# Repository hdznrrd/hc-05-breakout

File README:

HC-05 Breakout

Breakout board for the popular HC-05 Bluetooth 2.0 module.

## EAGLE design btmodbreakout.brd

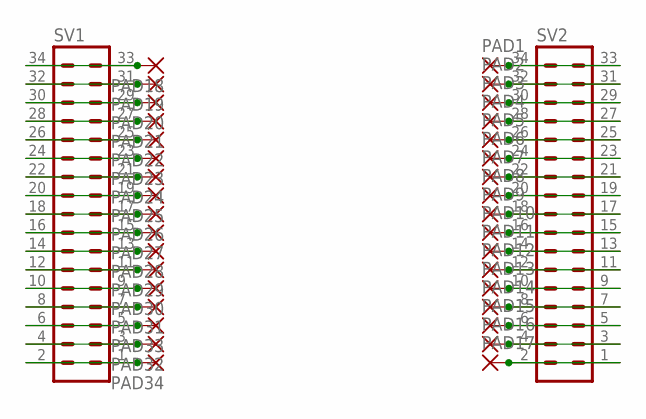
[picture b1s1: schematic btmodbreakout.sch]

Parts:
PAD1, PAD2, PAD3, PAD4, PAD5, PAD6, PAD7, PAD8, PAD9, PAD10, PAD11, PAD12, PAD13, PAD14, PAD15, PAD16, PAD17, PAD18, PAD19, PAD20, PAD21, PAD22, PAD23, PAD24, PAD25, PAD26, PAD27, PAD28, PAD29, PAD30, PAD31, PAD32, PAD33, PAD34: SMD2; SMD1,27-2,54
SV1, SV2: MA17-2

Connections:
unnamed: PAD18.1, SV1.33, SV1.34
unnamed: PAD19.1, SV1.31, SV1.32
unnamed: PAD20.1, SV1.29, SV1.30
unnamed: PAD21.1, SV1.27, SV1.28
unnamed: PAD22.1, SV1.25, SV1.26
unnamed: PAD23.1, SV1.23, SV1.24
unnamed: PAD24.1, SV1.21, SV1.22
unnamed: PAD25.1, SV1.19, SV1.20
unnamed: PAD26.1, SV1.17, SV1.18
unnamed: PAD27.1, SV1.15, SV1.16
unnamed: PAD28.1, SV1.13, SV1.14
unnamed: PAD29.1, SV1.11, SV1.12
unnamed: PAD30.1, SV1.9, SV1.10
unnamed: PAD31.1, SV1.7, SV1.8
unnamed: PAD33.1, SV1.5, SV1.6
unnamed: PAD32.1, SV1.3, SV1.4
unnamed: PAD34.1, SV1.1, SV1.2
unnamed: PAD1.1, SV2.33, SV2.34
unnamed: PAD2.1, SV2.31, SV2.32
unnamed: PAD3.1, SV2.29, SV2.30
unnamed: PAD4.1, SV2.27, SV2.28
unnamed: PAD5.1, SV2.25, SV2.26
unnamed: PAD6.1, SV2.23, SV2.24
unnamed: PAD7.1, SV2.21, SV2.22
unnamed: PAD8.1, SV2.19, SV2.20
unnamed: PAD9.1, SV2.17, SV2.18
unnamed: PAD10.1, SV2.15, SV2.16
unnamed: PAD11.1, SV2.13, SV2.14
unnamed: PAD12.1, SV2.11, SV2.12
unnamed: PAD13.1, SV2.9, SV2.10
unnamed: PAD14.1, SV2.7, SV2.8
unnamed: PAD15.1, SV2.5, SV2.6
unnamed: PAD16.1, SV2.3, SV2.4
unnamed: PAD17.1, SV2.1, SV2.2

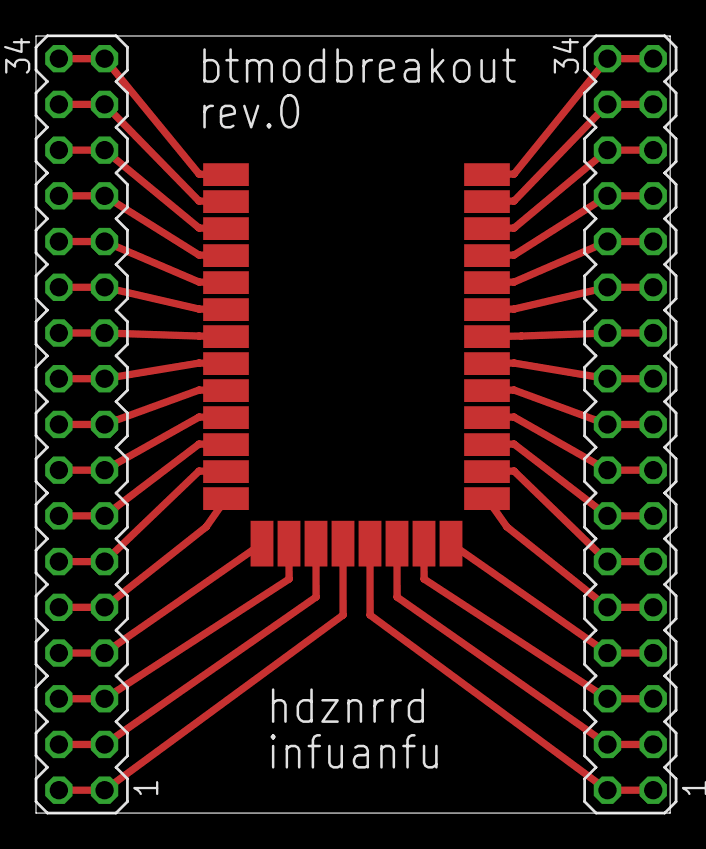
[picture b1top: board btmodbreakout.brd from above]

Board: 2 copper layers, 35.2 x 43.2 mm, 36 parts (0 on the bottom side), 34 nets.
